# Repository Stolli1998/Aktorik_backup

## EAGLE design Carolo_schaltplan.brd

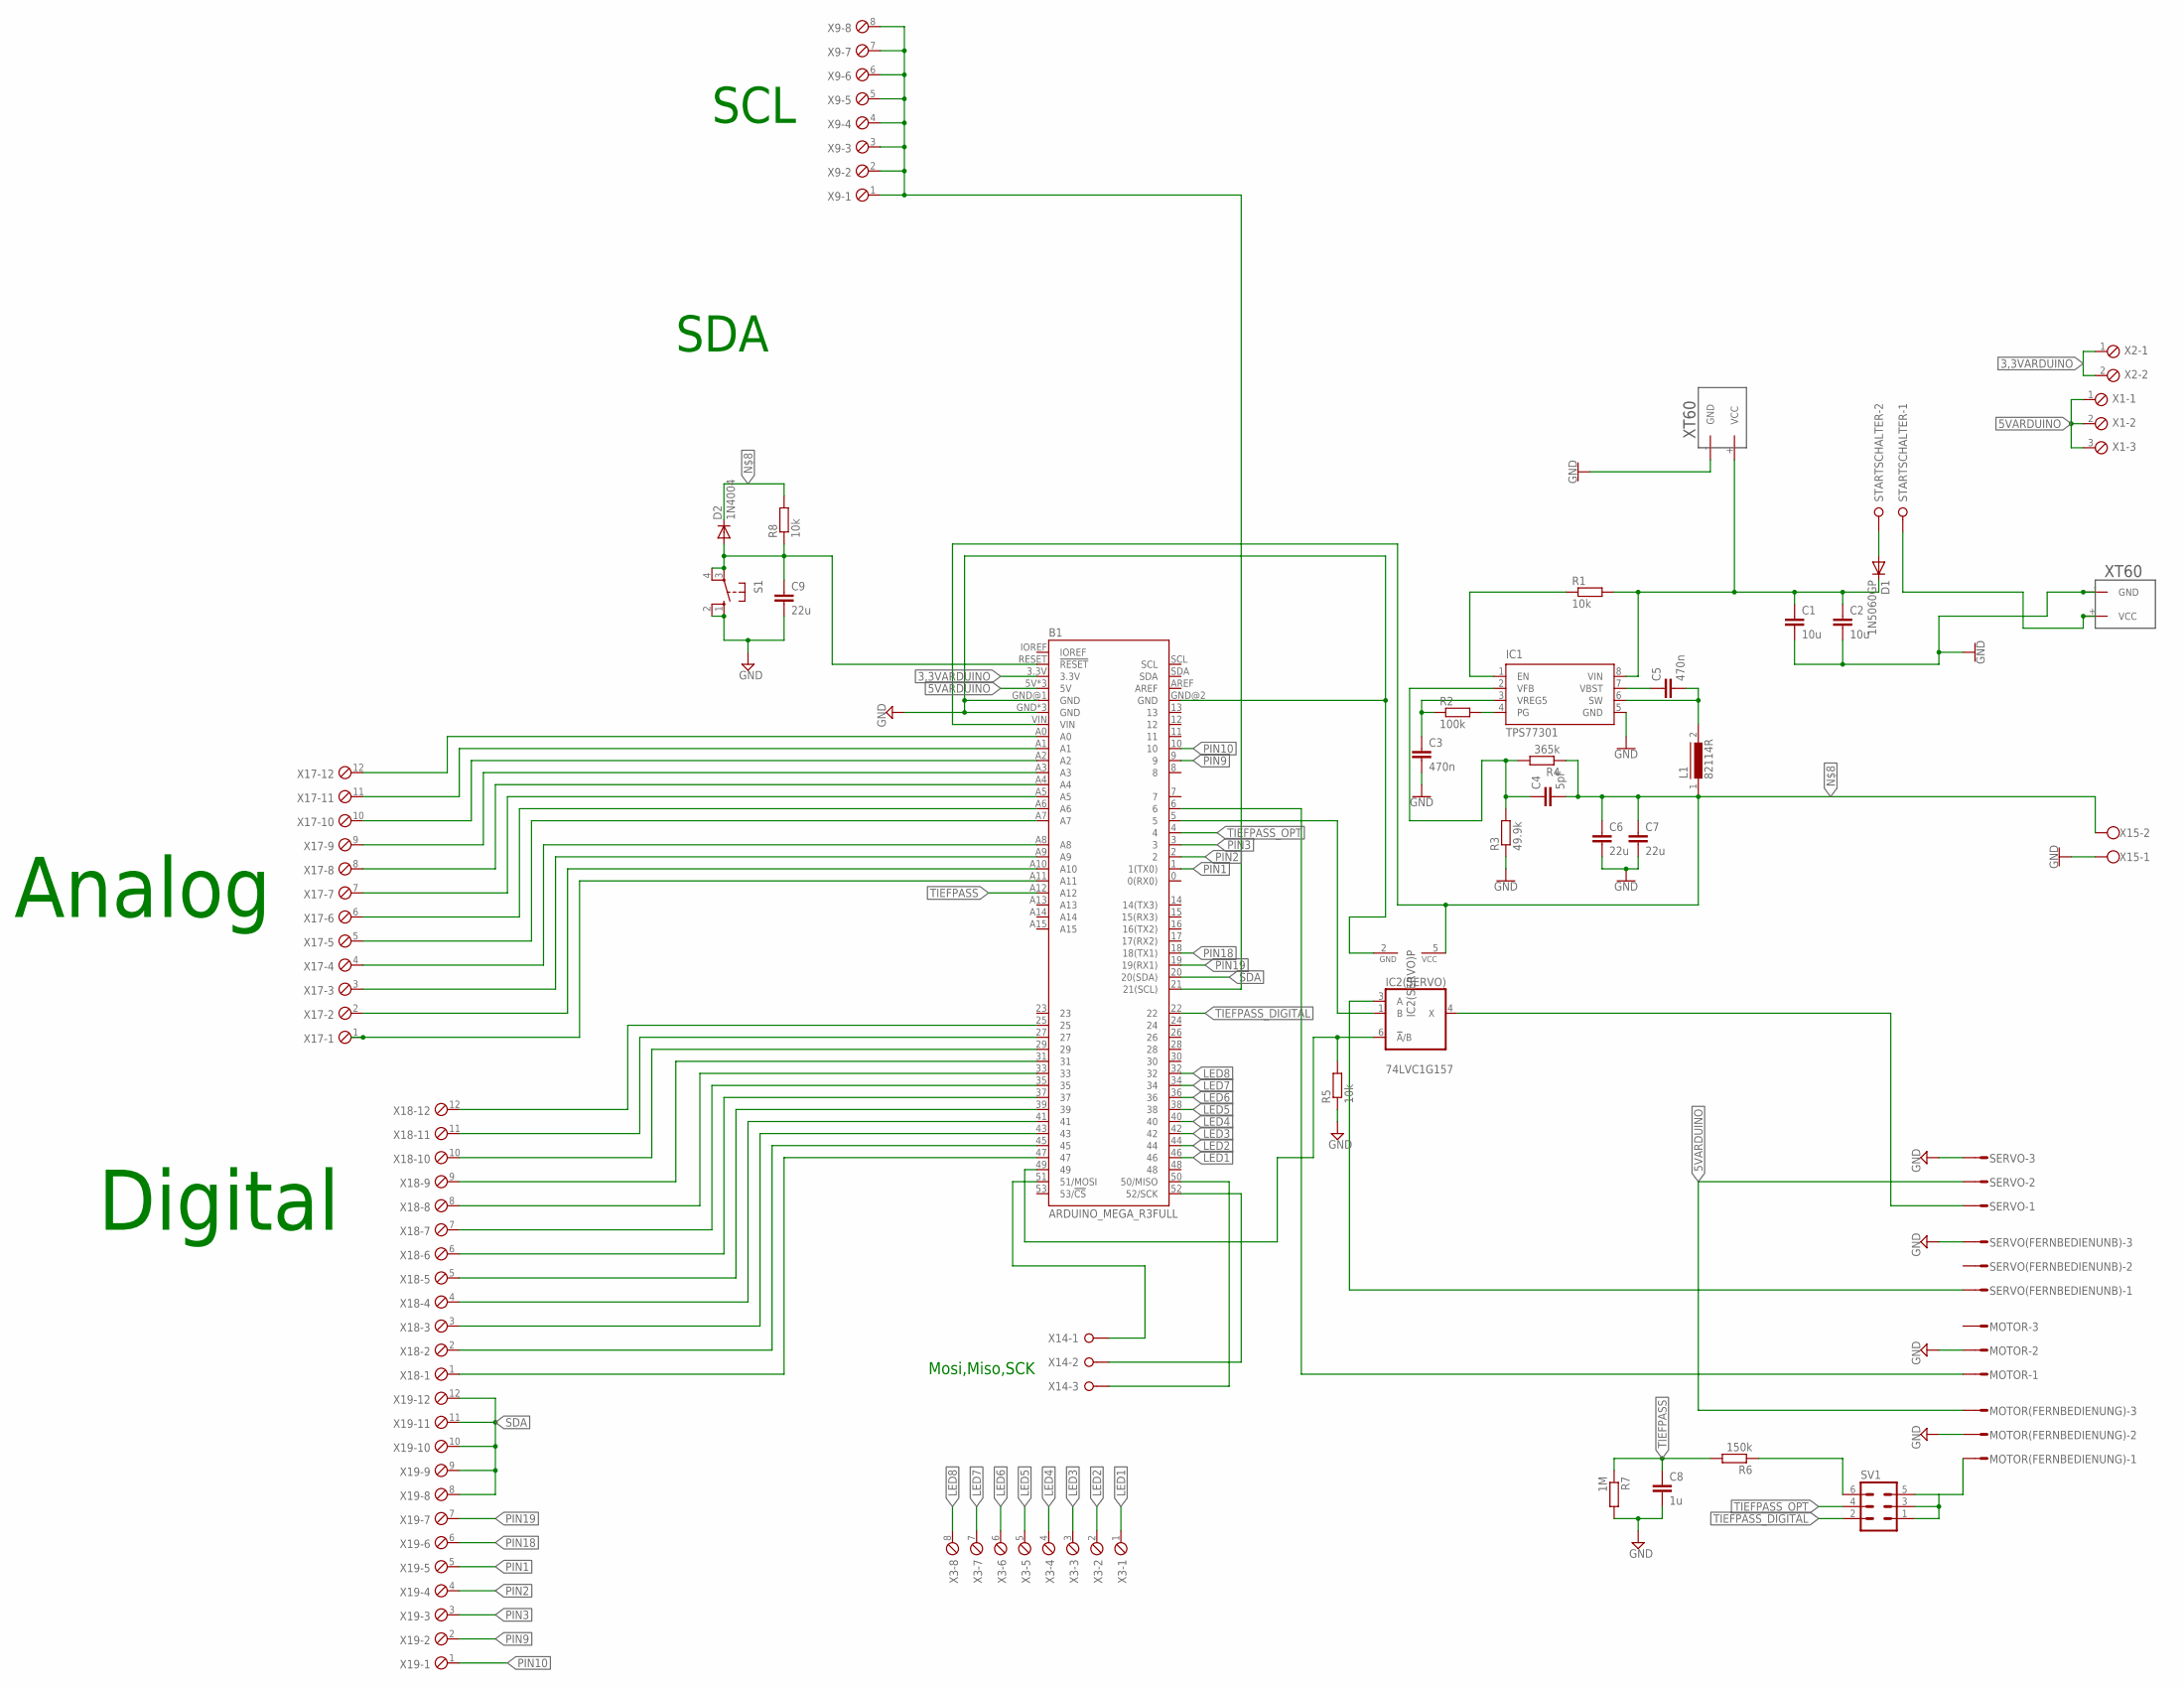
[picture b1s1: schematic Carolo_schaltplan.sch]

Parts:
B1: ARDUINO_MEGA_R3FULL; ARDUINO_MEGA_NO_SILK
C1, C2: 10u; C5B2.5
C3, C5: 470n; C5B2.5
C4: 5pF; C5B2.5
C6, C7, C9: 22u; C5B2.5
C8: 1u; C5B2.5
D1: 1N5060GP; DO15-12
D2: 1N4004; DO41-10
IC1: TPS77301; SOP-08
IC2(SERVO): 74LVC1G157; DBV_R-PDSO-G6
L1: 82114R
MOTOR: L03P
MOTOR(FERNBEDIENUNG): L03P
R1, R5, R8: 10k; 0309/12
R2: 100k; 0309/12
R3: 49.9k; 0309/12
R4: 365k; 0309/12
R6: 150k; 0309/12
R7: 1M; 0309/12
S1: 10-XX; B3F-10XX
SERVO: L03P
SERVO(FERNBEDIENUNB): L03P
STARTSCHALTER: W237-02P; W237-132
SV1: ML6
U$1, U$2: XT60
X1: MPT3; 3POL254
X2: MPT2; 2POL254
X3, X9: MPT8; 8POL254
X14: W237-03P; W237-133
X15: W237-102
X17, X18, X19: MPT12; 12POL254

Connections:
3,3VARDUINO: B1.3.3V, X2.1, X2.2
5VARDUINO: B1.5V, B1.5V@1 (5V), B1.5V@2 (5V), MOTOR(FERNBEDIENUNG).3, SERVO.2, X1.1, X1.2, X1.3
D22: B1.25, X18.12
D24: B1.29, X18.10
D26: B1.33, X18.8
GND: B1.GND, B1.GND@1 (GND), B1.GND@2 (GND), B1.GND@3 (GND), B1.GND@4 (GND), C1.2, C2.2, C3.2, C6.2, C7.2, C8.2, C9.2, IC1.5 (GND), IC2(SERVO).2 (GND), MOTOR.2, MOTOR(FERNBEDIENUNG).2, R3.1, R5.1, R7.2, S1.1 (S), S1.2 (S1), SERVO.3, SERVO(FERNBEDIENUNB).3, U$1.- (GND), U$2.- (GND), X15.1
LED1: B1.46, X3.1
LED2: B1.44, X3.2
LED3: B1.42, X3.3
LED4: B1.40, X3.4
LED5: B1.38, X3.5
LED6: B1.36, X3.6
LED7: B1.34, X3.7
LED8: B1.32, X3.8
unnamed: B1.RESET (!RESET), C9.1, D2.A, R8.1, S1.3, S1.4 (P1)
unnamed: C1.1, C2.1, D1.C, IC1.8 (VIN), R1.2, U$2.+ (VCC)
unnamed: C4.1, IC1.2 (VFB), R3.2, R4.2
unnamed: IC1.4 (PG), R2.2
unnamed: B1.27, X18.11
unnamed: C5.1, IC1.7 (VBST)
unnamed: B1.VIN, C4.2, C6.1, C7.1, D2.C, IC2(SERVO).5 (VCC), L1.1, R4.1, R8.2, X15.2
unnamed: B1.A0, X17.12
unnamed: STARTSCHALTER.1, U$1.+ (VCC)
unnamed: B1.31, X18.9
unnamed: IC2(SERVO).4 (X), SERVO.1
unnamed: B1.5, IC2(SERVO).1 (B)
unnamed: D1.A, STARTSCHALTER.2
unnamed: IC2(SERVO).3 (A), SERVO(FERNBEDIENUNB).1
unnamed: B1.6, MOTOR.1
unnamed: B1.A2, X17.10
unnamed: B1.A3, X17.9
unnamed: B1.A4, X17.8
unnamed: B1.A5, X17.7
unnamed: B1.A6, X17.6
unnamed: B1.A7, X17.5
unnamed: B1.A8, X17.4
unnamed: B1.A9, X17.3
unnamed: B1.A10, X17.2
unnamed: B1.A11, X17.1
unnamed: B1.35, X18.7
unnamed: B1.21 (21(SCL)), X9.1, X9.2, X9.3, X9.4, X9.5, X9.6, X9.7, X9.8
unnamed: B1.37, X18.6
unnamed: B1.39, X18.5
unnamed: B1.41, X18.4
unnamed: B1.43, X18.3
unnamed: B1.45, X18.2
unnamed: B1.47, X18.1
unnamed: B1.52 (52/SCK), X14.2
unnamed: R6.1, SV1.6
unnamed: MOTOR(FERNBEDIENUNG).1, SV1.1, SV1.3, SV1.5
unnamed: IC1.1 (EN), R1.1
unnamed: B1.51 (51/MOSI), X14.1
unnamed: B1.50 (50/MISO), X14.3
unnamed: C5.2, IC1.6 (SW), L1.2
unnamed: C3.1, IC1.3 (VREG5), R2.1
unnamed: B1.A1, X17.11
PIN1: B1.1 (1(TX0)), X19.5
PIN2: B1.2, X19.4
PIN3: B1.3, X19.3
PIN9: B1.9, X19.2
PIN10: B1.10, X19.1
PIN18: B1.18 (18(TX1)), X19.6
PIN19: B1.19 (19(RX1)), X19.7
SDA: B1.20 (20(SDA)), X19.8, X19.9, X19.10, X19.11, X19.12
SL: B1.49, IC2(SERVO).6 (!A!/B), R5.2
TIEFPASS: B1.A12, C8.1, R6.2, R7.1
TIEFPASS_DIGITAL: B1.22, SV1.2
TIEFPASS_OPT: B1.4, SV1.4

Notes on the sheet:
Analog
Digital
SDA
SCL
Mosi,Miso,SCK

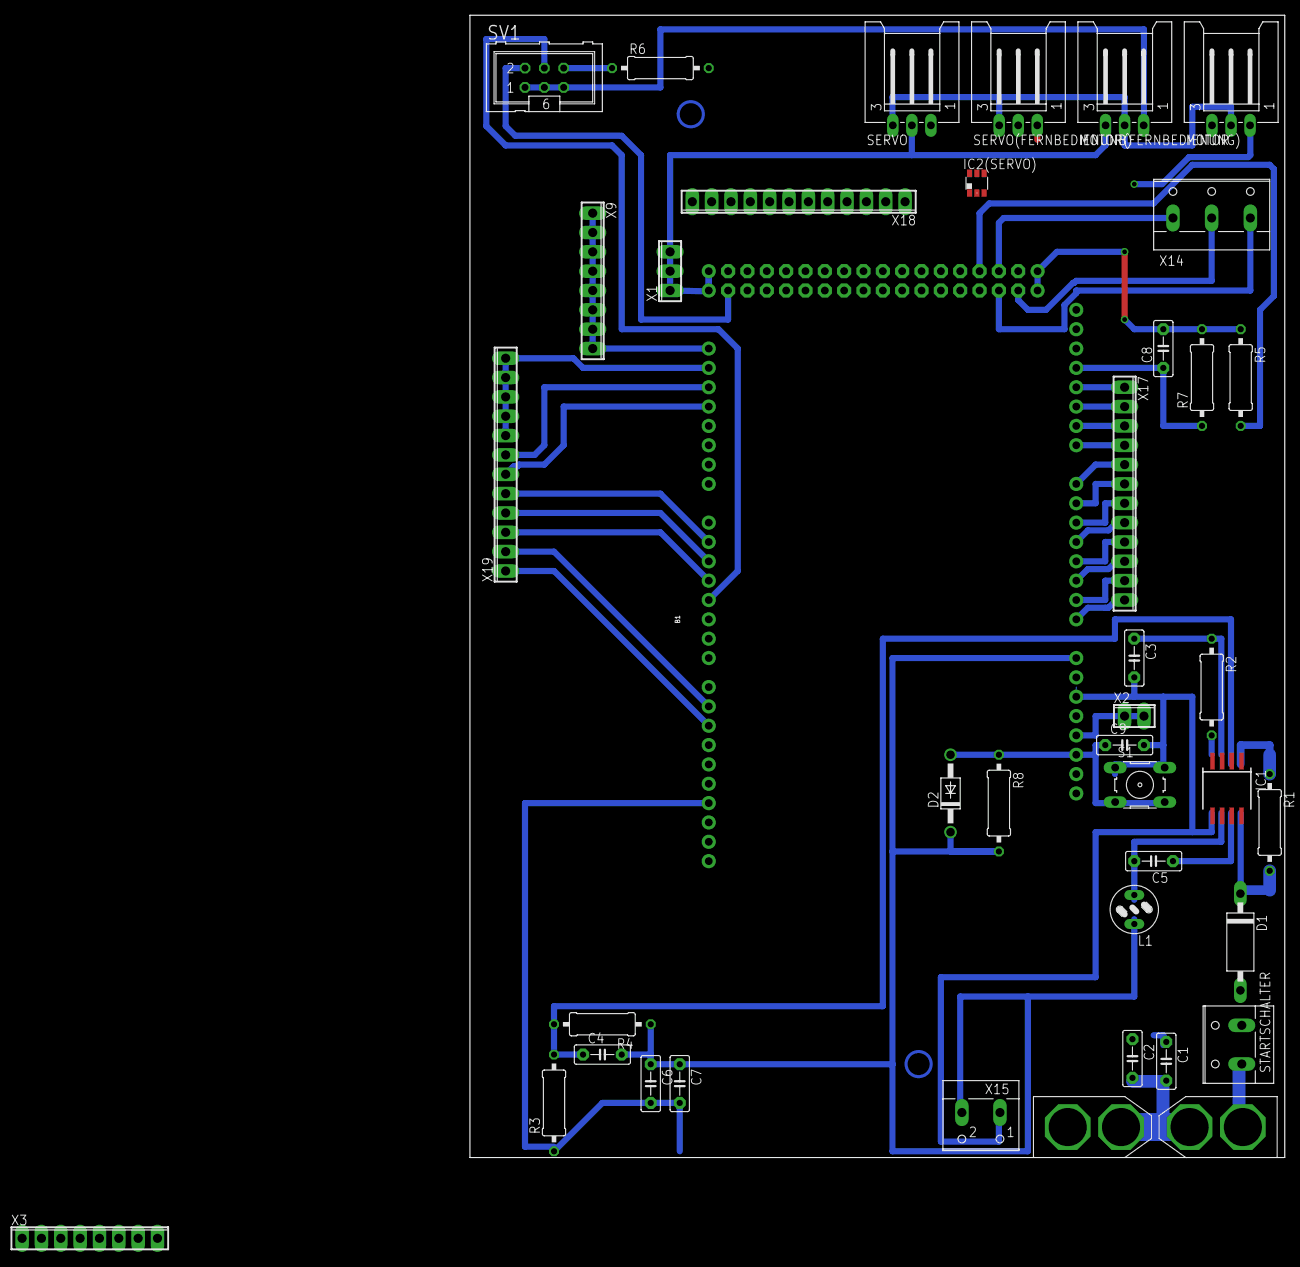
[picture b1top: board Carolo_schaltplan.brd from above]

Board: 2 copper layers, 107.0 x 150.0 mm, 41 parts (0 on the bottom side), 68 nets.

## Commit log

2020-01-23 hochladen

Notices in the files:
parts and their libraries:
SparkFun-Boards: Licensing: Creative Commons ShareAlike 4.0 International - https://creativecommons.org/licenses/by-sa/4.0
